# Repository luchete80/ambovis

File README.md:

# Proyecto RespirAR UBA

## Ventilador Mecánico Mínimo (VMM)
El VMM es un proyecto nacido en la Facultad de Ingeniería de la Universidad de Buenos Aires y tiene como objetivo crear un prototipo de respirador de bajo costo. [Leer más](https://www.fi.uba.ar/noticias/desarrollo-de-insumos-y-equipamiento-medico-3984)

En este repositorio encontrará el codigo escrito en C++ junto con la documentación de:
- [Manuales](docs/manuals/README.md)
  - [Preparación del entorno y ejecución del código](docs/manuals/development-setup.md)
  - [Uso del menú del dipositivo](docs/manuals/menu/README.md)
- [Recursos de investigación](docs/resources/README.md)
  - [Esquemáticos](docs/resources/schematics)
  - [Recursos de lectura](docs/resources/help%20sources)
  - [Simulador arduino tft](docs/resources/tft_simulator.md)
- [Calidad de software](docs/test/README.md)
  - [Pruebas manuales](docs/test)
  - [Pruebas unitarias](docs/test/unit_tests.md)
- [Contribución](docs/contributing/README.md)

## Funcionalidades

Las funcionalidades cubiertas por el sistema hasta el momento son:
- Funcionamiento del sistema con alimentación alterna o por batería
- Modo reposo del sistema
- Configuración de parámetros: BPM, IE, Volumen
- Configuración de valores de alarmas: PIP, PEEP, VM
- Visualización de parametros: PIP, PEEP, VM
- Visualización de gráficas de presión y flujo
- Visualización de carga de batería
- Visualizacion de alarmas: en pantalla, sonido y por indicador luminoso
- Guardado en memoria de ciertas configuraciones

## Contacto

Por consultas, enviar un email a [respirar@fi.uba.ar](mailto:respirar@fi.uba.ar?subject=[RespirAR])

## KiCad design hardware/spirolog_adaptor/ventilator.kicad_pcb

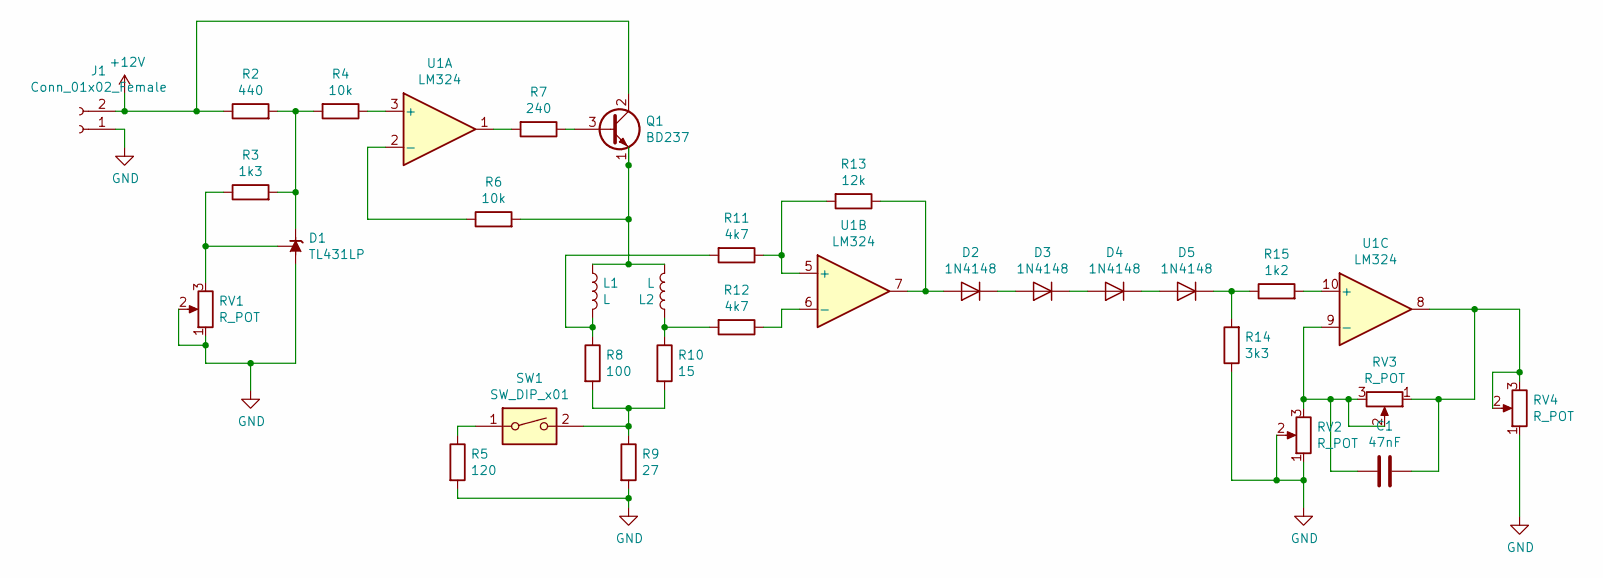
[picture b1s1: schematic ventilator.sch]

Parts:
C1: 47nF; C_Disc_D3.0mm_W2.0mm_P2.50mm
D1: TL431LP; TO-92_Inline
D2, D3, D4, D5: 1N4148; D_DO-35_SOD27_P7.62mm_Horizontal
J1: Conn_01x02_Female; TerminalBlock_MetzConnect_Type055_RT01502HDWU_1x02_P5.00mm_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
L1, L2: L; TerminalBlock_MetzConnect_Type055_RT01502HDWU_1x02_P5.00mm_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
Q1: BD237; TO-126-3_Vertical
R2: 440; R_Axial_DIN0207_L6.3mm_D2.5mm_P7.62mm_Horizontal
R3: 1k3; R_Axial_DIN0207_L6.3mm_D2.5mm_P7.62mm_Horizontal
R4, R6: 10k; R_Axial_DIN0207_L6.3mm_D2.5mm_P7.62mm_Horizontal
R5: 120; R_Axial_DIN0207_L6.3mm_D2.5mm_P7.62mm_Horizontal
R7: 240; R_Axial_DIN0207_L6.3mm_D2.5mm_P7.62mm_Horizontal
R8: 100; R_Axial_DIN0207_L6.3mm_D2.5mm_P7.62mm_Horizontal
R9: 27; R_Axial_DIN0207_L6.3mm_D2.5mm_P7.62mm_Horizontal
R10: 15; R_Axial_DIN0207_L6.3mm_D2.5mm_P7.62mm_Horizontal
R11, R12: 4k7; R_Axial_DIN0207_L6.3mm_D2.5mm_P7.62mm_Horizontal
R13: 12k; R_Axial_DIN0207_L6.3mm_D2.5mm_P7.62mm_Horizontal
R14: 3k3; R_Axial_DIN0207_L6.3mm_D2.5mm_P7.62mm_Horizontal
R15: 1k2; R_Axial_DIN0207_L6.3mm_D2.5mm_P7.62mm_Horizontal
RV1, RV2, RV3, RV4: R_POT; Potentiometer_Bourns_3266Y_Vertical
SW1: SW_DIP_x01; SW_PUSH_6mm
U1: LM324; DIP-16_W10.16mm

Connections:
+12V: J1.2, Q1.2 (C), R2.1
GND: D1.2 (A), J1.1, R5.2, R9.2, R14.1, RV1.1, RV1.2, RV2.1, RV2.2, RV4.1
unnamed: C1.1, RV3.1, RV4.2, RV4.3, U1.8
unnamed: C1.2, RV2.3, RV3.2, RV3.3, U1.9 (-)
unnamed: D1.1 (REF), R3.1, RV1.3
unnamed: D1.3 (K), R2.2, R3.2, R4.2
unnamed: D2.1 (K), D3.2 (A)
unnamed: D2.2 (A), R13.1, U1.7
unnamed: D3.1 (K), D4.2 (A)
unnamed: D4.1 (K), D5.2 (A)
unnamed: D5.1 (K), R14.2, R15.1
unnamed: L1.1, L2.2, Q1.1 (E), R6.2
unnamed: L1.2, R8.1, R11.2
unnamed: L2.1, R10.1, R12.2
unnamed: Q1.3 (B), R7.1
unnamed: R4.1, U1.3 (+)
unnamed: R5.1, SW1.1
unnamed: R6.1, U1.2 (-)
unnamed: R7.2, U1.1
unnamed: R8.2, R9.1, R10.2, SW1.2
unnamed: R11.1, R13.2, U1.5 (+)
unnamed: R12.1, U1.6 (-)
unnamed: R15.2, U1.10 (+)

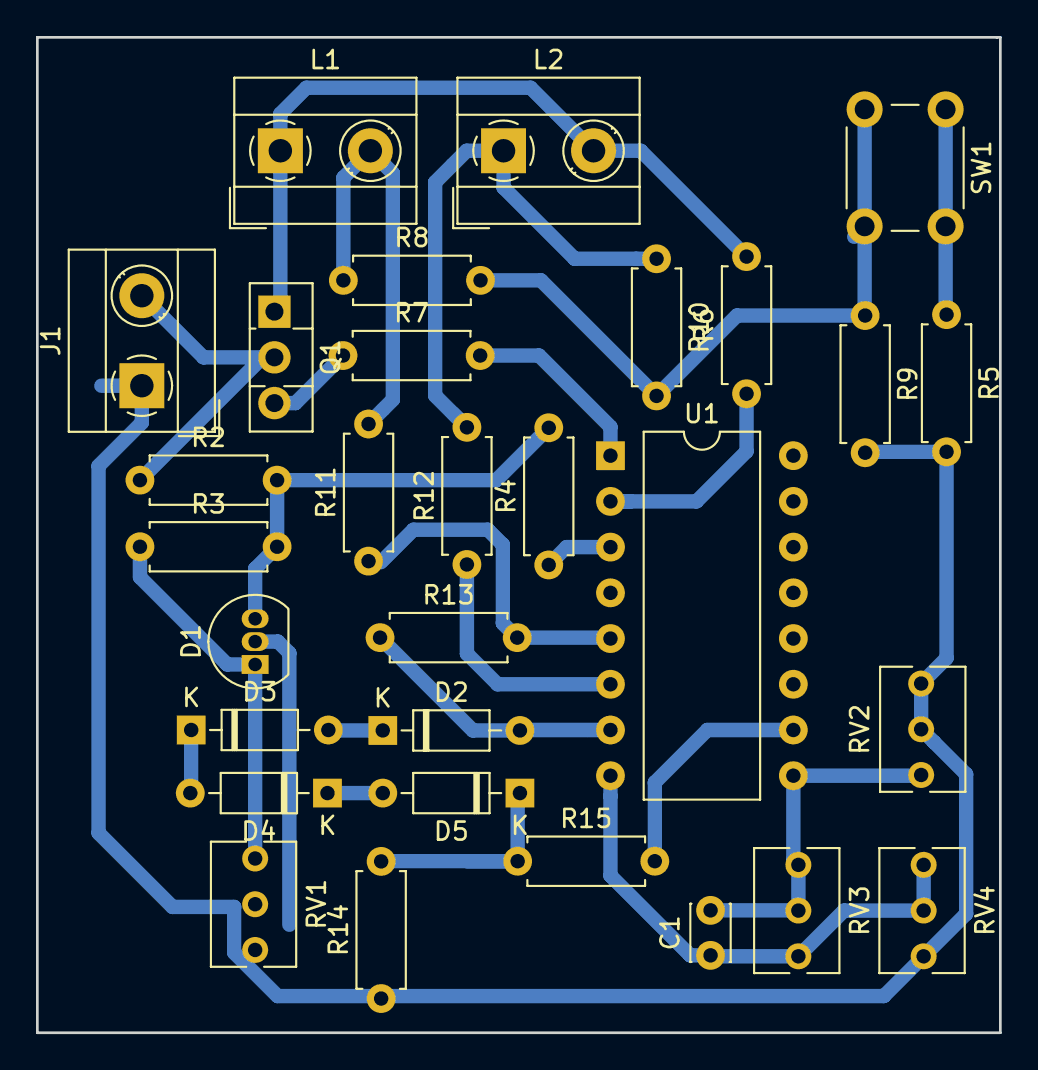
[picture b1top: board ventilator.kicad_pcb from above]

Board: 2 copper layers, 53.5 x 55.3 mm, 30 parts (0 on the bottom side), 23 nets.

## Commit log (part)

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2020-08-19 buzzer inverted
2020-08-19 buzzer put low at setup
2020-08-19 buzzer muted at BEGINING of setup
2020-08-19 fixed flow_f
2020-08-19 v1.0.9
2020-08-19 changed cam angle
2020-08-19 fixed pressure
2020-08-21 commented buzzer alarm
2020-08-21 inverted buzzer again
2020-08-21 fxied cam
2020-08-27 inverted buzzer, back to trim and battery percentage changed posiution display
2020-09-07 added 4 screen
2020-09-11 added experimental pressure correction
2020-09-22 changed min IE to 1
2020-10-02 added sleep mode
2020-10-02 changed display legend
2020-10-05 added
2020-10-06 see changelog
2020-10-06 changed legend
2020-10-14 inverted buzzer
2020-10-26 added tft example
2020-10-29 typho
2020-11-03 changed arduino
2020-11-03 working on arduino_sec
2020-11-04 added serial data to mega
2020-11-11 working pressure
2020-11-11 added serial reception from ambovis to update menu, test
2020-11-11 working change bpm
2020-11-12 dunno
2020-11-12 added to change menu only once per cycle
2020-11-12 working on #59
2020-11-17 working on alarms #68
2020-11-17 trabajando en #68
2020-11-18 cleaning
2020-11-18 trabajando en #71
2020-11-19 trabajando en 74
2020-11-19 trabajando en #74
2020-11-19 trabajando en #77
2020-12-02 fixed some definitios
2020-12-02 corrected flux receivig
2020-12-02 la lectura ahora es todo el tiempo, y el graficador solo filtra
2020-12-03 filtro de maxima diferencia de presiones no esta funcionando bien
2020-12-04 trabajando en #80
2020-12-04 trabajando en #84, parece que 25 ms van bien
2020-12-04 cod alternativo
2020-12-04 this closes #85
2020-12-09 se aumenta a 10 veces el envio serie
2020-12-09 agregadas peep y pip
2020-12-09 agregada version
2020-12-09 this closes #87
2020-12-10 added control comments
2020-12-10 this closes #88
2020-12-10 agregado muestreo ejemplo
2020-12-10 added version
2020-12-10 added test led, added version legend
2020-12-11 comenzando a trabajar en menu inicial
2020-12-17 Trabajando en #60
2020-12-17 trabajando en menu inicial
2020-12-29 this closes #98
2020-12-29 working on #91
2021-01-04 added first menus
2021-01-04 menu opts
2021-01-06 trabajando en #100
2021-02-10 added sleep pins
2021-02-23 added sleep
2021-03-01 added schematics
2021-03-01 This closes #99
2021-03-01 this closes ##97
2021-03-10 Habilitado Pin SLEEP
2021-03-10 added serial ut
2021-03-10 muted buzzer
2021-03-11 Ths closes #105
2021-03-25 buzzer muted
2021-03-25 fixed commented muted buzzer
2021-03-25 Trabajando en #102, bjando vy a sigue el salto de pasos
2021-03-29 Volviendo hacia version funcional
2021-05-11 reemplazado por funcional
2021-05-11 agregados backups
2021-05-26 Menu ahora no interfiere con el respoirador. closes #118
2021-05-26 removidos algunos debugs
2021-05-29 Add gitignore and some comments
2021-06-02 comments and variable grouping
2021-06-08 closes #120
2021-06-12 more comments
2021-07-06 this closes #120
2021-08-12 first attempt for data collector
2021-08-12 missing files
2021-08-16 added readme for tests
2021-08-20 Commented default constructor
2021-09-05 remove flexy stepper and unused comments in mechVentilation.cpp
2021-09-19 added tests for MechVentilator.
2021-09-19 remove unused def
2021-10-03 added more tests
2021-10-19 Cambio de 16 micropasos, CAMBIAR A ACCEL STEPPER MAS ADELANT
2021-10-23 revert FlexyStepper removal, fix unit tests
2021-10-23 add gitginore file
2021-10-23 add macro to supress pid interaction when testing
2021-10-23 rename macro name
2021-11-09 using timer 1 and three for ventilation & stepper respectively, according to https://gitlab.com/reesistencia/reespirator/-/blob/dev/rees_firmware/rees_firmware.ino
2021-11-09 THIS IS WORKING ON NEW DRIVER; WITHOUT LOOSING STEPS, WITH GRAPHICS OK, AND MENU OK
2021-11-09 added max speed and accel to menu
2021-11-16 Updated Version 2.0.1
2021-11-16 add default Test vars
2021-11-22 fix compilation errors
2021-11-22 remove commented code
2021-11-23 trabajando en #122, colocando perifericos al final
2021-11-23 cambiada leyenda de volumenes de lugar
2021-11-23 Changing curve cleaning, this closes #123
2021-11-23 2 Cycles in main TFT. This closes #125
2021-11-30 move files and variable refactor
2021-11-30 converting to INTERNAL
2021-12-04 missing code
2021-12-14 fixed voltage variations in mpx sensor
2021-12-21 remove duplicated code
2021-12-21 adding sleep pin
2021-12-21 changing lcd sleep pin
2022-01-30 create systemState struct
2022-02-02 more refactors after testing code in the lab
2022-02-08 adding docs
2022-02-08 changing vzero in debug messages
2022-02-08 deleted old code
2022-02-08 deleting old code of verror
2022-02-08 reduce batery level reading count
2022-02-08 dunnno
2022-02-19 refactors in ambovis file
2022-02-27 extract dpflux to another file, remove unused code
2022-03-01 extracted functions to testable files
2022-03-01 correct code in wrong place
2022-03-01 rename header and remove commented code
2022-03-05 revert change
2022-04-19 added power off messages
2022-04-19 This closes #133
2022-04-20 added calibration cycles
2022-04-20 added devblog
2022-04-21 Added initial menu
2022-04-21 this closes #140
2022-04-22 started motor after
2022-04-28 changed batery resistors
2022-04-28 Working with battery
2022-05-11 nuevo menu sin usar en ambovis.
2022-05-12 removed Pid class and sensor header that was unused
2022-05-13 added poweroff ok, initial menu and TFT corrections
2022-05-15 chnage files from directory, removed unused files. Also some var cleaning
2022-05-22 rebase master with develop features
2022-05-24 added PIN_STEPPER
2022-05-24 added delay
2022-06-11 refactors
2022-07-03 added Menu v2 and helper modules
2022-07-09 refactor for the new menu - menuV2- without the initial setup
2022-07-30 use struct variables in the general code and remove old external variables
2022-07-30 remove serial log
2022-08-04 Reparado TFT inicial con garbage de fonfo
2022-08-04 mensaje inicial tft
2022-08-04 restaurada lectura adc0
2022-08-04 limpieza de tft inicial
2022-08-10 add log for mechVentilation
2022-08-10 commented sleep mode not working. Restore calibration cycle
2022-08-11 pasando el background de corte de energia a negro. cambiando el fondo de print vols a negro
2022-08-11 cambiando tamaño de rectangulos de background
2022-08-11 se agrega detencion del motor en sleep mode
2022-08-11 limpieza de tft despues de calibracion
2022-08-11 manual
2022-08-11 mejorando los graficos de presion
2022-08-11 corrgiiendo correccion de ciclos
2022-08-13 remove serial outputs
2022-08-13 undo changes in non used files
2022-08-13 remove most of the unused variables and classes not used
2022-08-14 remove not needed changes
2022-08-14 undo deletion
2022-08-15 remove commented variables to clean code
2022-08-15 add .gitignore
2022-08-15 Brought changes from the LAME local machine to the current develop branch
2022-08-15 remove unused constants and extra code in menu inic
2022-08-18 Corregido error de calibracion critico. Eliminadas cuentas de verror que no se utiliza luego de calibrar
2022-08-18 cambiado el modo sleep
2022-08-20 removed more unused code and macro validations
2022-08-20 remove unused println
2022-08-22 added new mechanical ventilation functions
2022-08-25 added battery and temp tests
2022-08-25 devlog, baterias y otros
2022-08-25 trabajando en sleep
2022-08-25 trabajando en sleep, devlog
2022-08-27 removed unused options and menu entries
2022-08-27 remove serial print
2022-08-27 restore level in display
2022-08-27 clean up
2022-08-27 extract calculations to a different functions
2022-08-28 use new mechanical ventilation implementation
2022-08-29 fix flag endedWhileMoving
2022-08-30 extract and use alarm validation function
2022-08-31 simplify alarm validation function
2022-09-02 extract sensor logic to separate module
2022-09-03 refactor in tft functions to receive tft as parameter and clean some code
2022-09-03 clean unused variable
2022-09-04 fix references and creation of mechanicalVentilation
2022-09-04 remove unused vars
2022-09-10 fix keyboard speed, go back to parameters after some time without inactivity
2022-09-10 fix compilation errors, removed sensordata as it was part of other ticket
2022-09-10 rename to VentilationParameters
2022-09-11 extract memory interaction to separate module
2022-09-11 some small fixes in tft function
2022-09-11 undo change in tft
2022-09-11 fix branch merge unused change
2022-09-22 cambiado fin de carrera para que no pise todo el tiempo
2022-09-29 added alarms, displat, mech ventilation changes
2022-10-20 volviendo a e834ae5d2a8c7d37b03c68e46f87a68fe2e49bb5
2022-11-03 Errores respecto a bc0e641a916d2b8a8cca44d9adc5e08934d7a53c, NO SE ENTIENDE QUE CAMBIOS HUBO
2022-11-21 refactor to isolate calibration logic and general refactors to avoid duplicated code
2022-11-24 clean variables and signatures
2022-11-27 changed menu implementation to use data structs to manage interaction and extracted logic in smaller functions
2022-12-22 remove commented lines
2022-12-24 clean code and extract initialization to functions
2022-12-29 remove a lot of commented code and unused vars
2022-12-29 move back state check function to right place
2022-12-29 move buzzer logic to alarms module
2023-01-28 attempt to run github actions and added EpoxyDuino dependency
2023-01-28 attempt to run unit test
2023-02-14 attempt to find Epoxyduino
2023-02-15 remove EPoxyDuino as dependency project
2023-02-15 attempt to run the first test
2023-02-15 correct test
2023-02-15 suppress make output - except errors
2023-02-20 clean and update required libs
2023-02-20 remove Aunit and LiquidCrystal
2023-02-20 add verbose
2023-02-20 test actions
2023-02-20 download deps in github actions
2023-02-20 update on SPI
2023-02-20 fix SPI
2023-03-12 use fun param instead of extern
2023-03-19 last fixes
2023-03-20 remove unused var
2023-03-25 small refactors
2023-03-26 rename vars to snake case
2023-03-26 change call to mech ventilation
2023-03-26 update dependency file Adafruit SPI device
2023-03-27 fix dep name
2023-03-27 fix import
2023-03-27 ignore deps
2023-03-27 try to replace epoxyDuino
2023-03-27 fix path
2023-03-27 create file
2023-03-28 resolve dup time, remove EpoxyDuino
2023-03-28 rebase RESP-develop in the branch
2023-03-28 rebase RESP-develop
2023-03-28 change var type
2023-04-01 refactors required for sensorcalculation tests to work
2023-04-01 remove extra space
2023-04-01 fix find flux test
2023-04-02 create custom makefile for EpoxyDuino and create target to run all tests
2023-04-02 gitignore eepromdatafile
2023-04-07 add mech Ventilation unit tests
2023-04-22 bump version develop into master
2023-04-22 bump version for develo changes
2023-04-26 home search final position change
2023-04-26 stepper lower revert to master value
2023-04-27 move config code
2023-04-27 fix order of params
2023-04-27 fix unit test
2023-04-29 remove settings menu, remove autopid and filter opions. filter is always on
2023-04-29 unify types to int8_t
2023-04-29 reorganize files and folders
2023-04-29 remove wrong files
2023-05-01 refactor on tft function
2023-05-01 add image and draft text for branch methodology
2023-05-01 add image path
2023-05-01 add tag, release sections and clean text
2023-05-06 script for Linux/OS to deploy changes in the board
2023-05-06 validate exit 1 in compilation
2023-05-06 add reference to source of solution for a bug
2023-05-06 add powershell script
2023-05-07 added deploy script for windows and readme updated
2023-05-21 refactors in menu.cpp to make tests, added unit tests
2023-05-21 change interruptions impl to flag impl
2023-05-22 make some refactors
2023-05-25 readme files, documentation WIP
2023-05-25 update gitignore
2023-05-26 attempt to write the intro readme
2023-05-26 rename files
2023-05-26 remove not needed files
2023-06-01 change folder name
2023-06-01 format fixes
2023-06-03 display the initial menu
2023-06-15 added test
2023-06-20 rename and use uint8 type
2023-06-20 fix test
2023-06-23 add print line
2023-06-25 add python script for deployment
2023-06-25 Update README.md
    Format readme
2023-06-25 fix readme files format
2023-06-27 clean unused line
2023-06-27 bump version
2023-07-03 minor fixes
2023-07-08 change version
2023-07-08 changed version to 2.1.0
2023-07-08 added image and links
2023-07-18 added screenshots
